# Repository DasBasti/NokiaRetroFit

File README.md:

# Nokia 3210 Retro Fit
Retrofitting a Nokia 3210 with new dual ARM core CPU

* 1GHz dual core CPU
* 1GB DDR3 RAM
* 8GB Memory
* Android N (N7.1.1_1.0.0)

# Status
	[---------100%] BOM generation  
	[--------80%--] Development of schematics / System design  
	[-----50%-----] Pinmuxing of i.MX7  
	[5%-----------] Board layout  
	[0%-----------] Android port  
	[0%-----------] Android applications

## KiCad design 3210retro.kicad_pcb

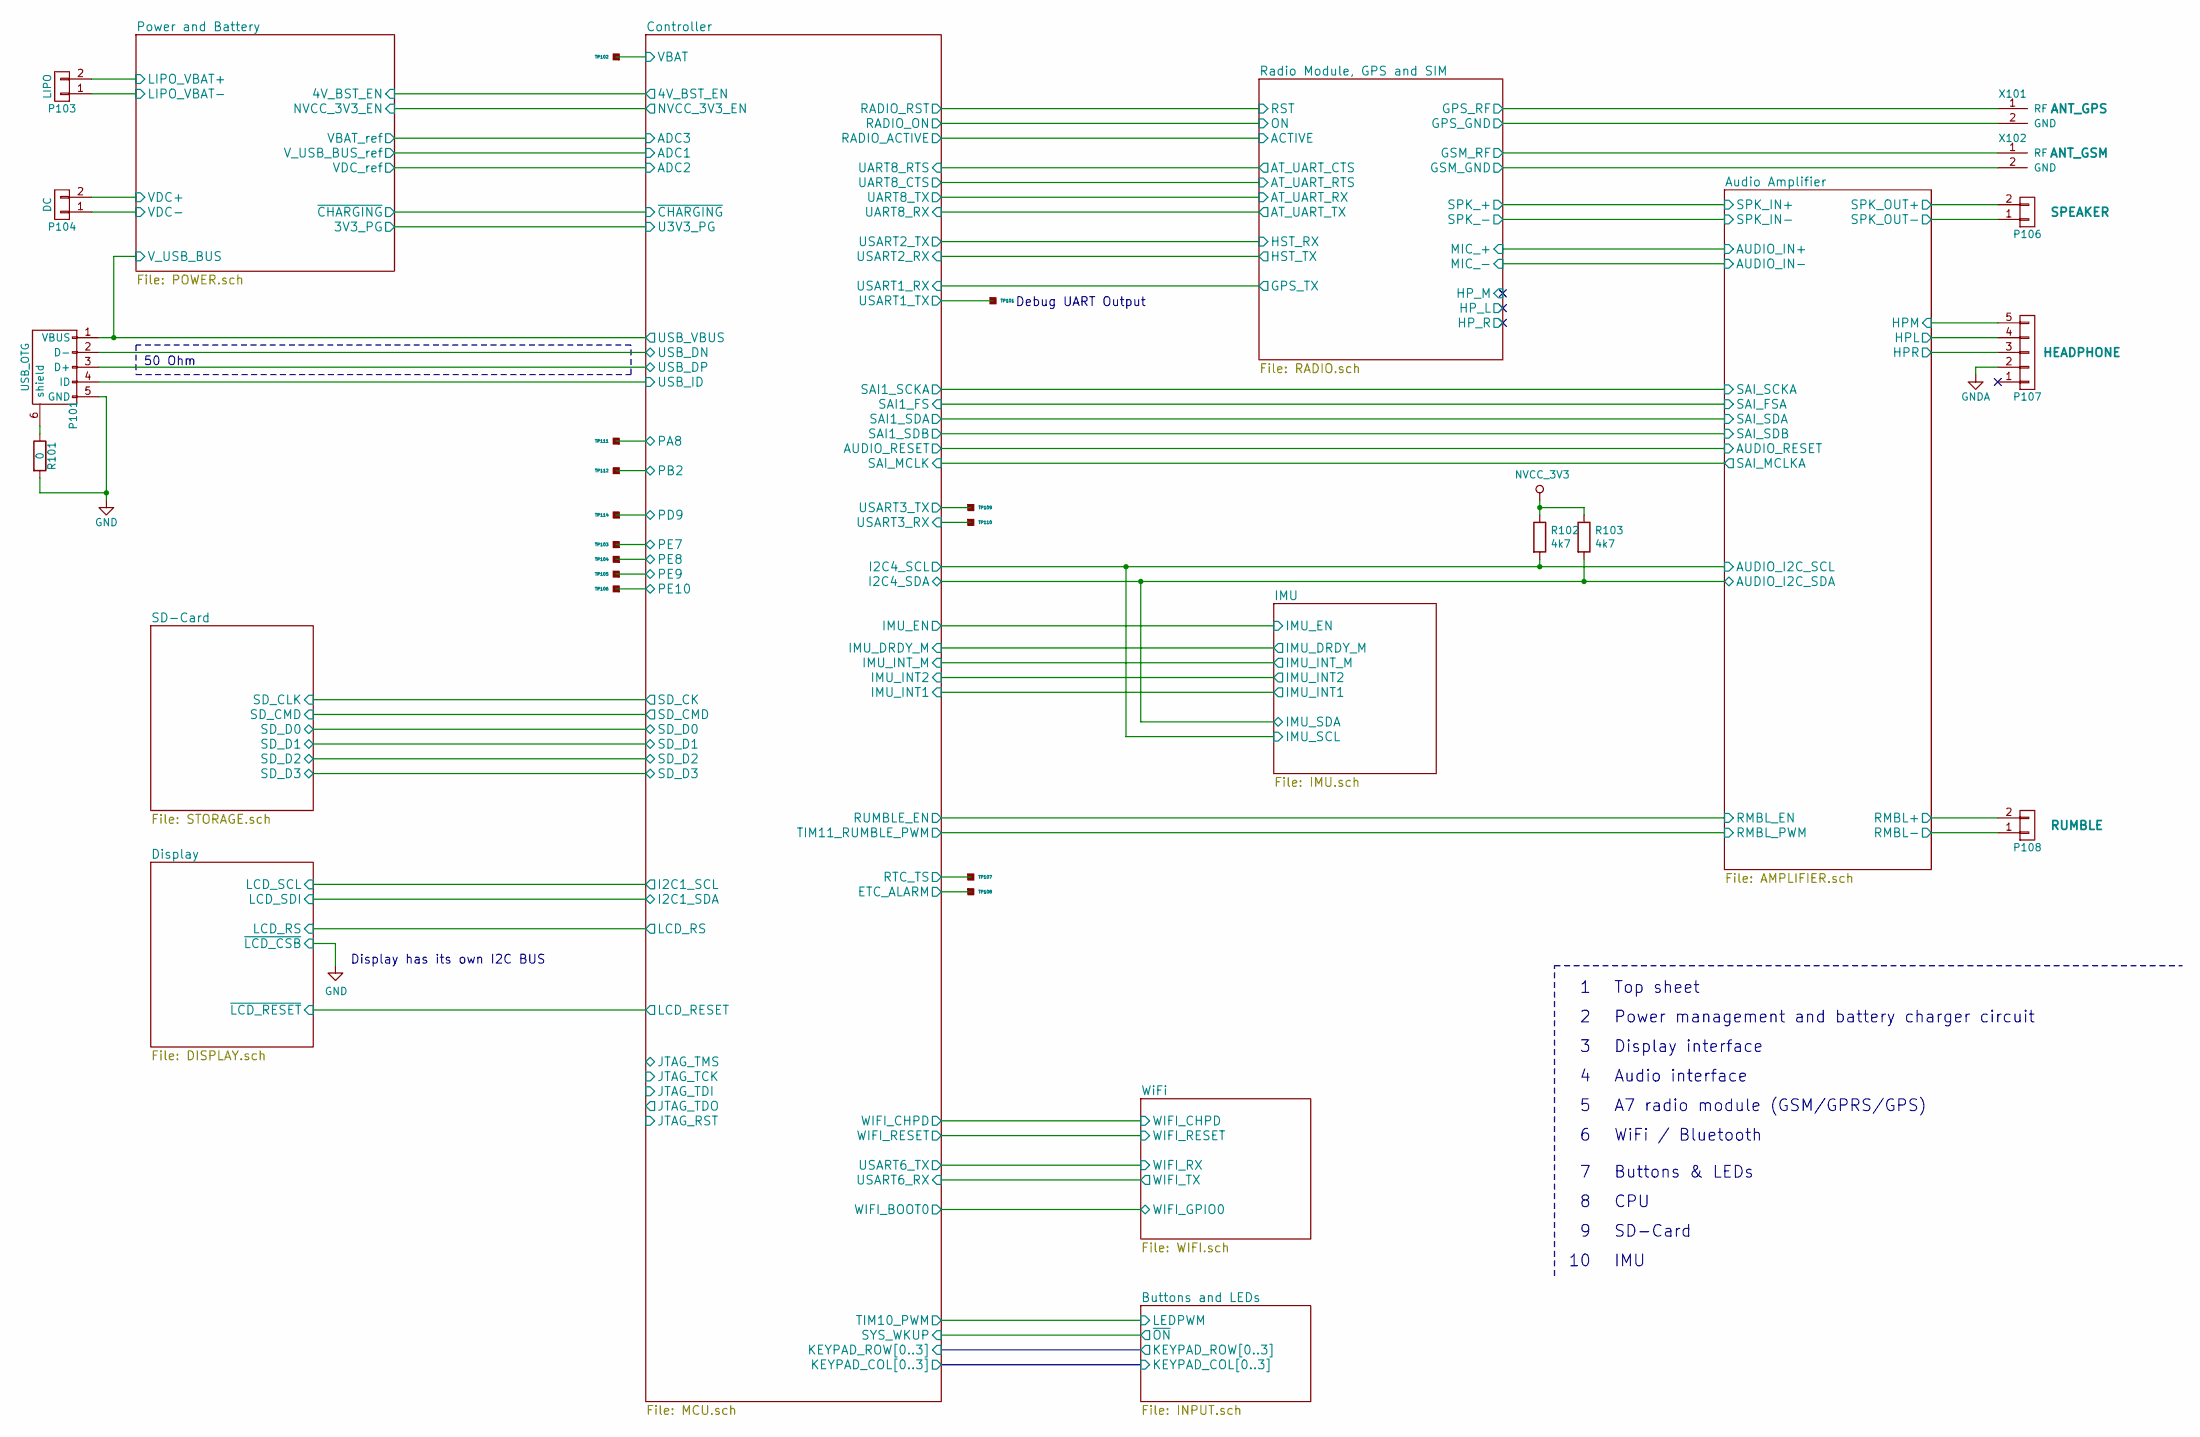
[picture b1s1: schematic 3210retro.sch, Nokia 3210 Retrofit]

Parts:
P101: USB_OTG; USB_Micro-B_10103594-0001LF
P103: LIPO; SolderWirePad_2x_0,8
P104: DC; SolderWirePad_2x_0,8
P106: SPEAKER; SolderWirePad_2x_0,8
P107: HEADPHONE; PJ_320_D
P108: RUMBLE; Rumble_Pads
R101: 0; R_0402_NoSilk
R102, R103: 4k7; R_0402_NoSilk
TP101, TP102, TP103, TP104, TP105, TP106, TP107, TP108, TP109, TP110, TP111, TP112, TP114: TP
X101: ANT_GPS; SolderWirePad_2x_0,8
X102: ANT_GSM; SolderWirePad_2x_0,8

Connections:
+5V: P101.1 (VBUS); also elsewhere on the board
+BATT_LIPO: P103.2; also elsewhere on the board
/Audio Amplifier/AUDIO_I2C_SCL: R102.2; also elsewhere on the board
/Audio Amplifier/AUDIO_I2C_SDA: R103.2; also elsewhere on the board
/Audio Amplifier/HPL: P107.4; also elsewhere on the board
/Audio Amplifier/HPR: P107.3; also elsewhere on the board
/Audio Amplifier/RMBL+: P108.2; also elsewhere on the board
/Audio Amplifier/RMBL-: P108.1; also elsewhere on the board
/Audio Amplifier/SPK_OUT+: P106.2; also elsewhere on the board
/Audio Amplifier/SPK_OUT-: P106.1; also elsewhere on the board
/Controller/ETC_ALARM: TP108.1; also elsewhere on the board
/Controller/PA8: TP111.1; also elsewhere on the board
/Controller/PB2: TP112.1; also elsewhere on the board
/Controller/PD9: TP114.1; also elsewhere on the board
/Controller/PE7: TP103.1; also elsewhere on the board
/Controller/PE8: TP104.1; also elsewhere on the board
/Controller/PE9: TP105.1; also elsewhere on the board
/Controller/PE10: TP106.1; also elsewhere on the board
/Controller/RTC_TS: TP107.1; also elsewhere on the board
/Controller/USART1_TX: TP101.1; also elsewhere on the board
/Controller/USART3_RX: TP110.1; also elsewhere on the board
/Controller/USART3_TX: TP109.1; also elsewhere on the board
/Controller/USB_DN: P101.2 (D-); also elsewhere on the board
/Controller/USB_DP: P101.3 (D+); also elsewhere on the board
/Controller/USB_ID: P101.4 (ID); also elsewhere on the board
/Controller/VBAT: TP102.1; also elsewhere on the board
/Power and Battery/VDC+: P104.2; also elsewhere on the board
/Radio Module, GPS and SIM/GPS_GND: X101.2 (GND); also elsewhere on the board
/Radio Module, GPS and SIM/GPS_RF: X101.1 (RF); also elsewhere on the board
/Radio Module, GPS and SIM/GSM_GND: X102.2 (GND); also elsewhere on the board
/Radio Module, GPS and SIM/GSM_RF: X102.1 (RF); also elsewhere on the board
GND: P101.5 (GND), P103.1, R101.2; also elsewhere on the board
GNDA: P107.2; also elsewhere on the board
GNDREF: P104.1; also elsewhere on the board
NVCC_3V3: R102.1, R103.1; also elsewhere on the board
unnamed: P101.6 (shield), R101.1

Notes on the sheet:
50 Ohm
Top sheet
Power management and battery charger circuit
Display interface
Audio interface
A7 radio module (GSM/GPRS/GPS)
WiFi / Bluetooth
Buttons & LEDs
CPU
Display has its own I2C BUS
Debug UART Output
SD-Card
IMU

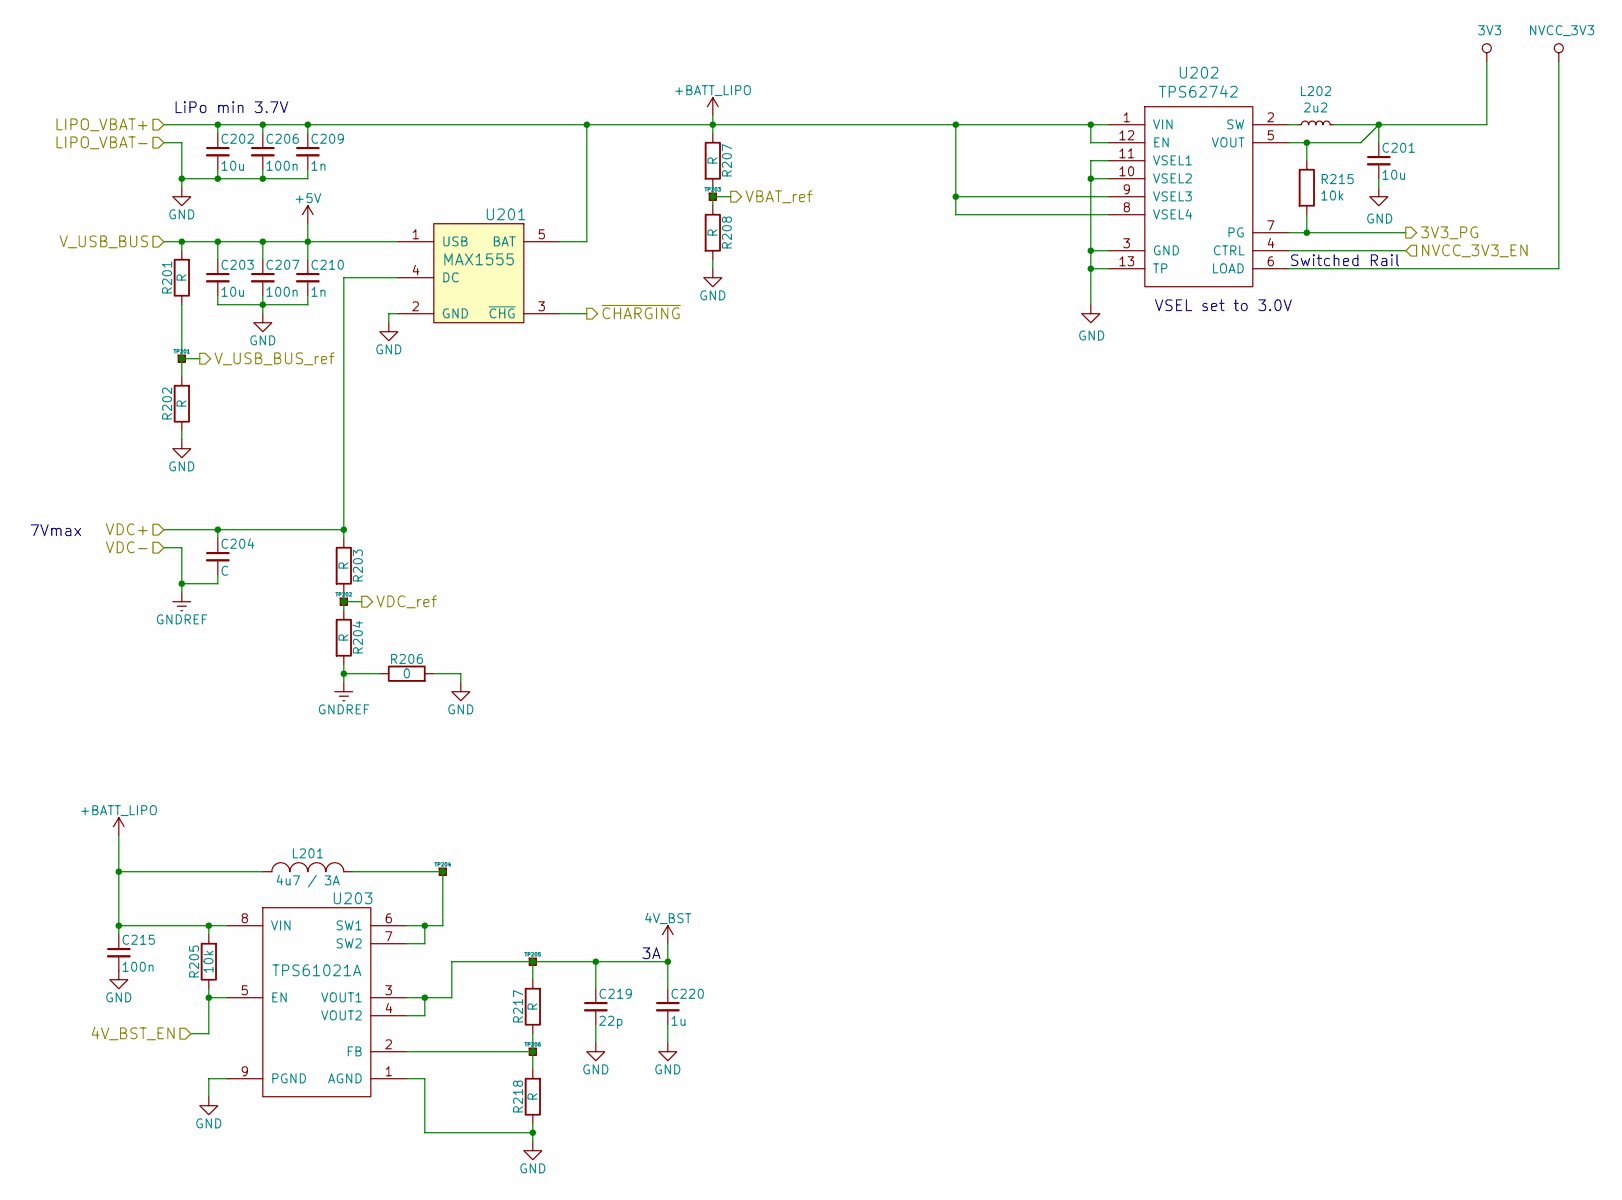
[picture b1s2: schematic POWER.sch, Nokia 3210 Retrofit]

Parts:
C201, C202, C203: 10u; C_0603
C204: C; C_0402_NoSilk
C206, C207, C215: 100n; C_0402_NoSilk
C209, C210: 1n; C_0402_NoSilk
C219: 22p; C_0402_NoSilk
C220: 1u; C_0402_NoSilk
L201: 4u7 / 3A; Choke_SMD_1206_Standard
L202: 2u2; Choke_SMD_1206_Standard
R201, R202, R203, R204, R207, R208, R217, R218: R; R_0402_NoSilk
R205, R215: 10k; R_0402_NoSilk
R206: 0; R_0603
TP201, TP202, TP203, TP204, TP205, TP206: TP
U201: MAX1555; SOT-23-5
U202: TPS62742; TPS6274x
U203: TPS61021A; Texas_S-PVSON-N8_NoThermalVias

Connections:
3V3: C201.1, L202.2, R215.1, U202.5 (VOUT); also elsewhere on the board
4V_BST: C219.1, C220.1, R217.2, TP205.1, U203.3 (VOUT1), U203.4 (VOUT2); also elsewhere on the board
+5V: C203.1, C207.1, C210.1, R201.2, U201.1 (USB); also elsewhere on the board
+BATT_LIPO: C202.1, C206.1, C209.1, C215.1, L201.1, R205.2, R207.1, U201.5 (BAT), U202.1 (VIN), U202.8 (VSEL4), U202.9 (VSEL3), U202.12 (EN), U203.8 (VIN); also elsewhere on the board
/Controller/4V_BST_EN: R205.1, U203.5 (EN); also elsewhere on the board
/Controller/ADC1: R201.1, R202.2, TP201.1; also elsewhere on the board
/Controller/ADC2: R203.2, R204.1, TP202.1; also elsewhere on the board
/Controller/ADC3: R207.2, R208.1, TP203.1; also elsewhere on the board
/Controller/NVCC_3V3_EN: U202.4 (CTRL); also elsewhere on the board
/Controller/~CHARGING: U201.3 (~CHG); also elsewhere on the board
/Power and Battery/3V3_PG: R215.2, U202.7 (PG); also elsewhere on the board
/Power and Battery/VDC+: C204.1, R203.1, U201.4 (DC); also elsewhere on the board
GND: C201.2, C202.2, C203.2, C206.2, C207.2, C209.2, C210.2, C215.2, C219.2, C220.2, R202.1, R206.2, R208.2, R218.1, U201.2 (GND), U202.3 (GND), U202.10 (VSEL2), U202.11 (VSEL1), U202.13 (TP), U203.1 (AGND), U203.9 (PGND); also elsewhere on the board
GNDREF: C204.2, R204.2, R206.1; also elsewhere on the board
NVCC_3V3: U202.6 (LOAD); also elsewhere on the board
unnamed: L201.2, TP204.1, U203.6 (SW1), U203.7 (SW2)
unnamed: L202.1, U202.2 (SW)
unnamed: R217.1, R218.2, TP206.1, U203.2 (FB)

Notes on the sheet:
LiPo min 3.7V
7Vmax
Switched Rail
VSEL set to 3.0V

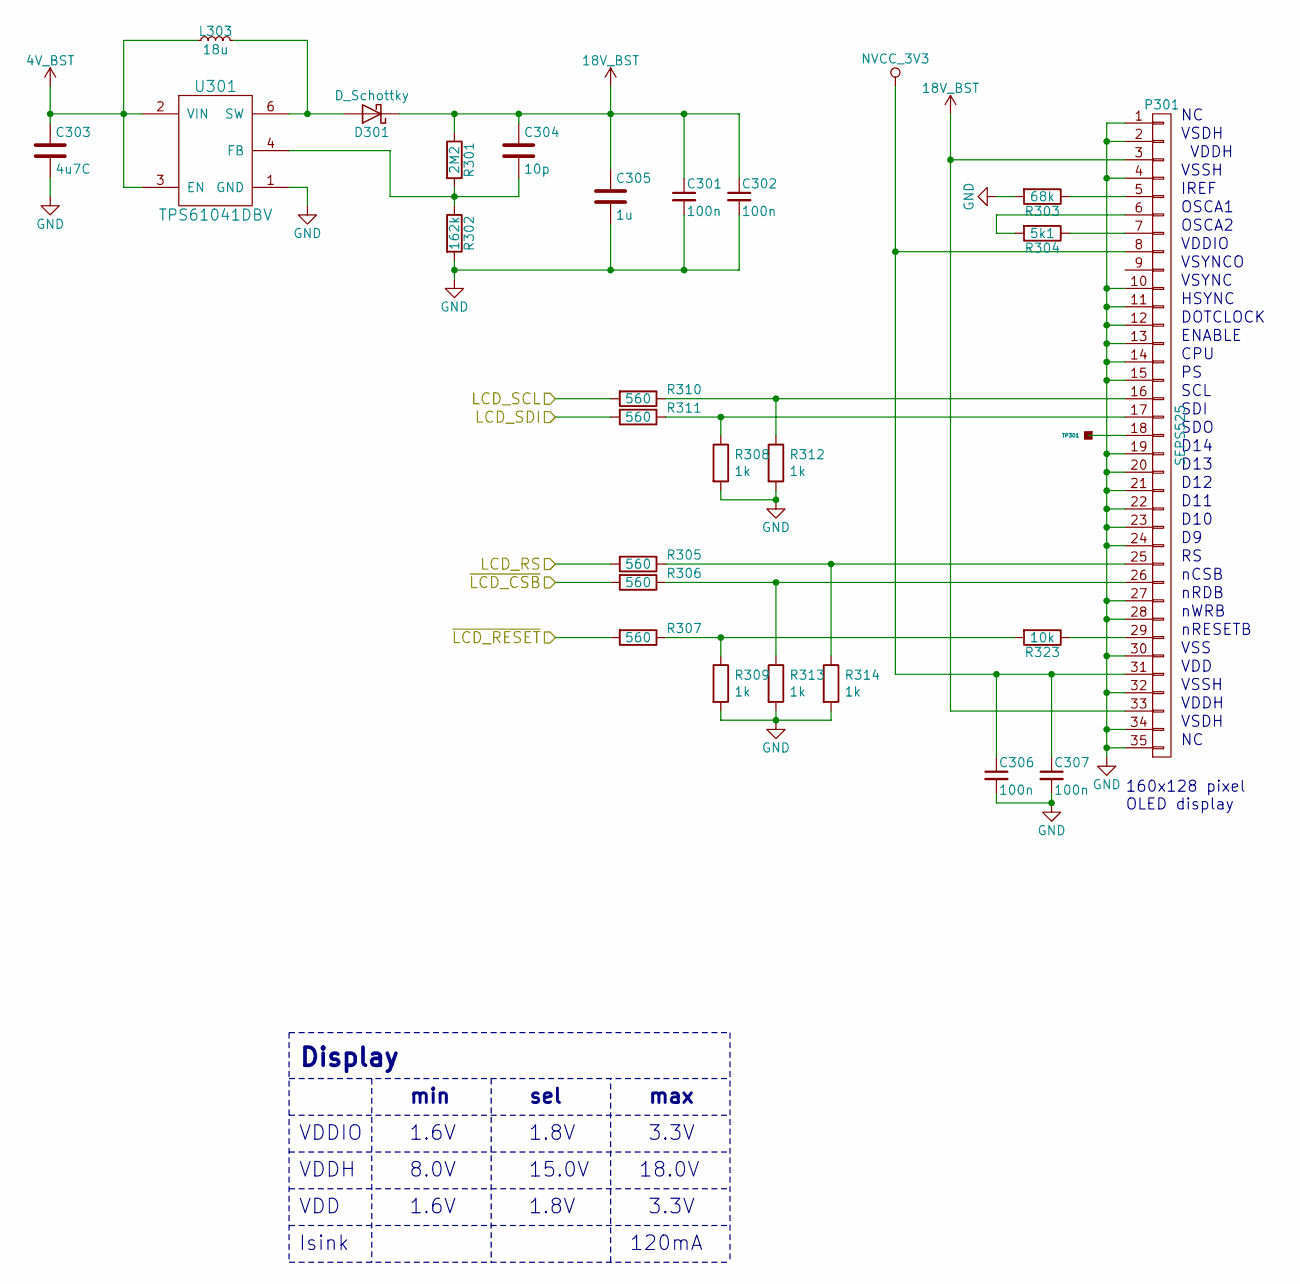
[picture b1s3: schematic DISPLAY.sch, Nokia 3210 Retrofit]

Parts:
C301, C302, C306, C307: 100n; C_0402_NoSilk
C303: 4u7C; C_0402_NoSilk
C304: 10p; C_0402_NoSilk
C305: 1u; C_0402_NoSilk
D301: D_Schottky; D_0805
L303: 18u; Choke_SMD_1206_Standard
P301: SEPS525; FFC-05-35
R301: 2M2; R_0402_NoSilk
R302: 162k; R_0402_NoSilk
R303: 68k; R_0402_NoSilk
R304: 5k1; R_0402_NoSilk
R305, R306, R307, R310, R311: 560; R_0402_NoSilk
R308, R309, R312, R313, R314: 1k; R_0402_NoSilk
R323: 10k; R_0402_NoSilk
TP301: TP
U301: TPS61041DBV; DFN-6-1EP_2x2mm_Pitch0.65mm

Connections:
4V_BST: C303.1, L303.2, U301.2 (VIN), U301.3 (EN); also elsewhere on the board
18V_BST: C301.1, C302.1, C304.1, C305.1, D301.1 (K), P301.3, P301.33, R301.1
/Controller/I2C1_SCL: R310.2; also elsewhere on the board
/Controller/I2C1_SDA: R311.2; also elsewhere on the board
/Controller/LCD_RESET: R307.2; also elsewhere on the board
/Controller/LCD_RS: R305.2; also elsewhere on the board
GND: C301.2, C302.2, C303.2, C305.2, C306.2, C307.2, P301.1, P301.2, P301.4, P301.10, P301.11, P301.12, P301.13, P301.14, P301.15, P301.19, P301.20, P301.21, P301.22, P301.23, P301.24, P301.27, P301.28, P301.30, P301.32, P301.34, P301.35, R302.2, R303.2, R306.2, R308.2, R309.2, R312.2, R313.2, R314.2, U301.1 (GND); also elsewhere on the board
NVCC_3V3: C306.1, C307.1, P301.8, P301.31; also elsewhere on the board
unnamed: C304.2, R301.2, R302.1, U301.4 (FB)
unnamed: D301.2 (A), L303.1, U301.6 (SW)
unnamed: P301.5, R303.1
unnamed: P301.6, R304.2
unnamed: P301.7, R304.1
unnamed: P301.16, R310.1, R312.1
unnamed: P301.17, R308.1, R311.1
unnamed: P301.18, TP301.1
unnamed: P301.25, R305.1, R314.1
unnamed: P301.26, R306.1, R313.1
unnamed: P301.29, R323.1
unnamed: R307.1, R309.1, R323.2

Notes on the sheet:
VDDIO
VDDH
VDD
Display
1.6V
3.3V
8.0V
18.0V
min
max
160x128 pixel OLED display
Isink
120mA
sel
1.8V
15.0V
VSDH
VSSH
IREF
OSCA1
OSCA2
VSYNCO
VSYNC
HSYNC
DOTCLOCK
ENABLE
CPU
SCL
SDI
SDO
D14
D13
D12
D11
D10
nCSB
nWRB
nRESETB
VSS
nRDB

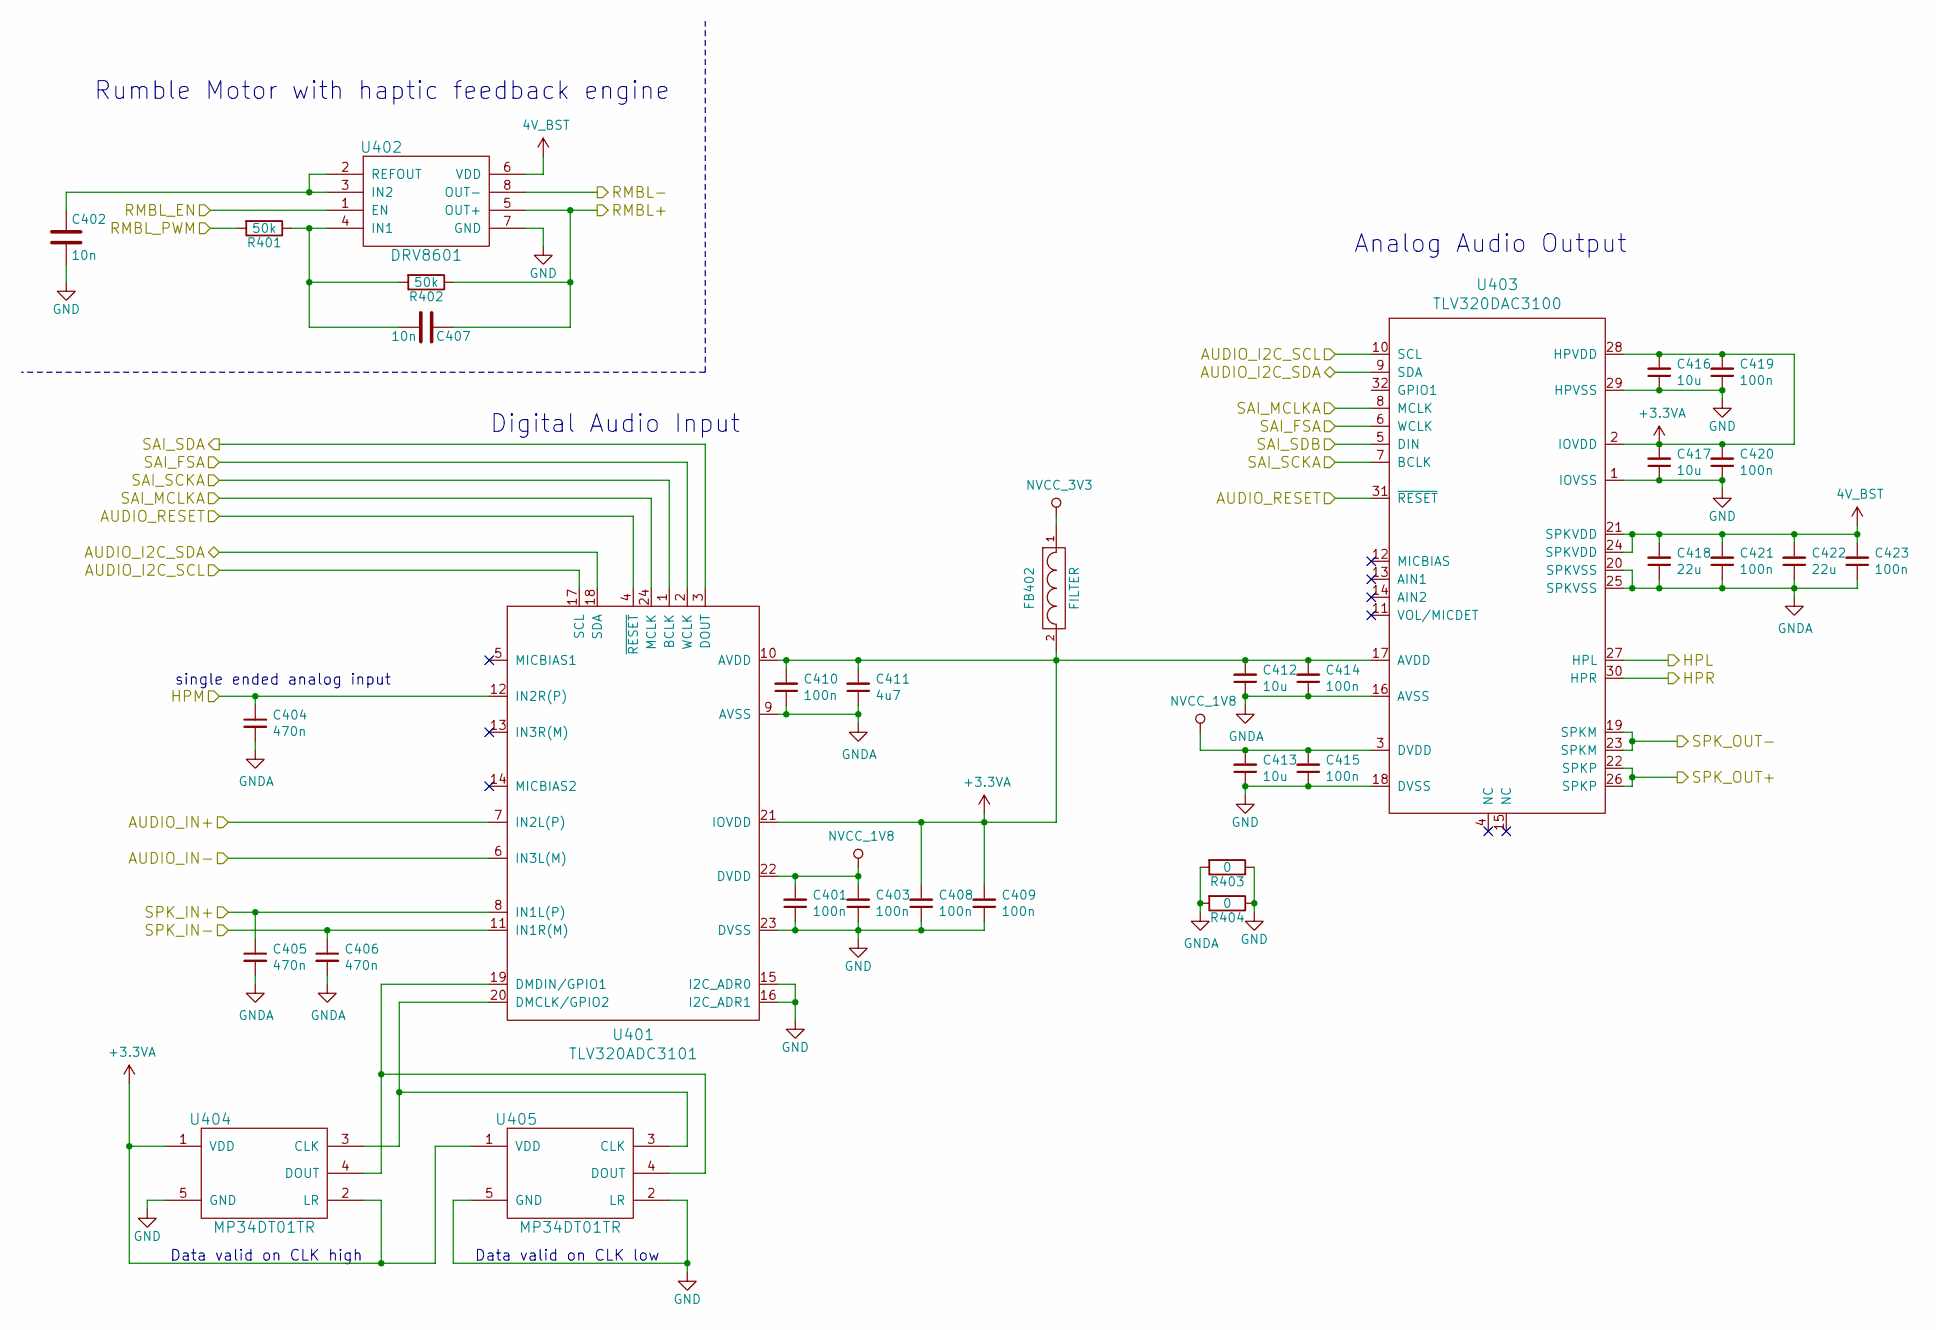
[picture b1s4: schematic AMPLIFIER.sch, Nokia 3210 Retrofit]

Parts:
C401, C403, C408, C409, C410, C414, C415, C419, C420, C421, C423: 100n; C_0402_NoSilk
C402, C407: 10n; C_0402_NoSilk
C404, C405, C406: 470n; C_0402_NoSilk
C411: 4u7; C_0402_NoSilk
C412, C413, C416, C417: 10u; C_0402_NoSilk
C418, C422: 22u; C_0402_NoSilk
FB402: FILTER; Choke_SMD_1206_Standard
R401, R402: 50k; R_0402_NoSilk
R403, R404: 0; R_0402_NoSilk
U401: TLV320ADC3101; QFN-24-1EP_4x4mm_Pitch0.5mm
U402: DRV8601; DFN-8-1EP_3x3mm_Pitch0.65mm
U403: TLV320DAC3100; QFN-32-1EP_5x5mm_Pitch0.5mm
U404, U405: MP34DT01TR; MP34DT01_NoGroundRing

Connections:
4V_BST: C418.2, C421.2, C422.2, C423.2, U402.6 (VDD), U403.21 (SPKVDD), U403.24 (SPKVDD); also elsewhere on the board
+3.3VA: C408.2, C409.2, C410.2, C411.2, C412.2, C414.2, C416.2, C417.2, C419.2, C420.2, FB402.2, U401.10 (AVDD), U401.21 (IOVDD), U403.2 (IOVDD), U403.17 (AVDD), U403.28 (HPVDD), U404.1 (VDD), U404.2 (LR), U405.1 (VDD)
/Audio Amplifier/AUDIO_I2C_SCL: U401.17 (SCL), U403.10 (SCL); also elsewhere on the board
/Audio Amplifier/AUDIO_I2C_SDA: U401.18 (SDA), U403.9 (SDA); also elsewhere on the board
/Audio Amplifier/AUDIO_IN+: U401.7 (IN2L(P)); also elsewhere on the board
/Audio Amplifier/AUDIO_IN-: U401.6 (IN3L(M)); also elsewhere on the board
/Audio Amplifier/AUDIO_RESET: U401.4 (~RESET), U403.31 (~RESET); also elsewhere on the board
/Audio Amplifier/HPL: U403.27 (HPL); also elsewhere on the board
/Audio Amplifier/HPM: C404.1, U401.12 (IN2R(P))
/Audio Amplifier/HPR: U403.30 (HPR); also elsewhere on the board
/Audio Amplifier/RMBL+: C407.1, R402.1, U402.5 (OUT+); also elsewhere on the board
/Audio Amplifier/RMBL-: U402.8 (OUT-); also elsewhere on the board
/Audio Amplifier/RMBL_EN: U402.1 (EN); also elsewhere on the board
/Audio Amplifier/RMBL_PWM: R401.2; also elsewhere on the board
/Audio Amplifier/SPK_OUT+: U403.22 (SPKP), U403.26 (SPKP); also elsewhere on the board
/Audio Amplifier/SPK_OUT-: U403.19 (SPKM), U403.23 (SPKM); also elsewhere on the board
/Controller/SAI1_FS: U401.2 (WCLK), U403.6 (WCLK); also elsewhere on the board
/Controller/SAI1_SCKA: U401.1 (BCLK), U403.7 (BCLK); also elsewhere on the board
/Controller/SAI1_SDA: U401.3 (DOUT); also elsewhere on the board
/Controller/SAI1_SDB: U403.5 (DIN); also elsewhere on the board
/Controller/SAI_MCLK: U401.24 (MCLK), U403.8 (MCLK); also elsewhere on the board
/Radio Module, GPS and SIM/SPK_+: C405.1, U401.8 (IN1L(P)); also elsewhere on the board
/Radio Module, GPS and SIM/SPK_-: C406.1, U401.11 (IN1R(M)); also elsewhere on the board
GND: C401.1, C402.2, C403.1, C408.1, C409.1, C413.1, C415.1, C416.1, C417.1, C419.1, C420.1, R403.1, R404.1, U401.15 (I2C_ADR0), U401.16 (I2C_ADR1), U401.23 (DVSS), U402.7 (GND), U402.9 (PAD), U403.1 (IOVSS), U403.18 (DVSS), U403.29 (HPVSS), U404.5 (GND), U405.2 (LR), U405.5 (GND); also elsewhere on the board
GNDA: C404.2, C405.2, C406.2, C410.1, C411.1, C412.1, C414.1, C418.1, C421.1, C422.1, C423.1, R403.2, R404.2, U401.9 (AVSS), U403.16 (AVSS), U403.20 (SPKVSS), U403.25 (SPKVSS); also elsewhere on the board
NVCC_1V8: C401.2, C403.2, C413.2, C415.2, U401.22 (DVDD), U403.3 (DVDD); also elsewhere on the board
NVCC_3V3: FB402.1; also elsewhere on the board
unnamed: C402.1, U402.2 (REFOUT), U402.3 (IN2)
unnamed: C407.2, R401.1, R402.2, U402.4 (IN1)
unnamed: U401.19 (DMDIN/GPIO1), U404.4 (DOUT), U405.4 (DOUT)
unnamed: U401.20 (DMCLK/GPIO2), U404.3 (CLK), U405.3 (CLK)

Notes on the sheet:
Data valid on CLK high
Data valid on CLK low
Rumble Motor with haptic feedback engine
single ended analog input
Digital Audio Input
Analog Audio Output

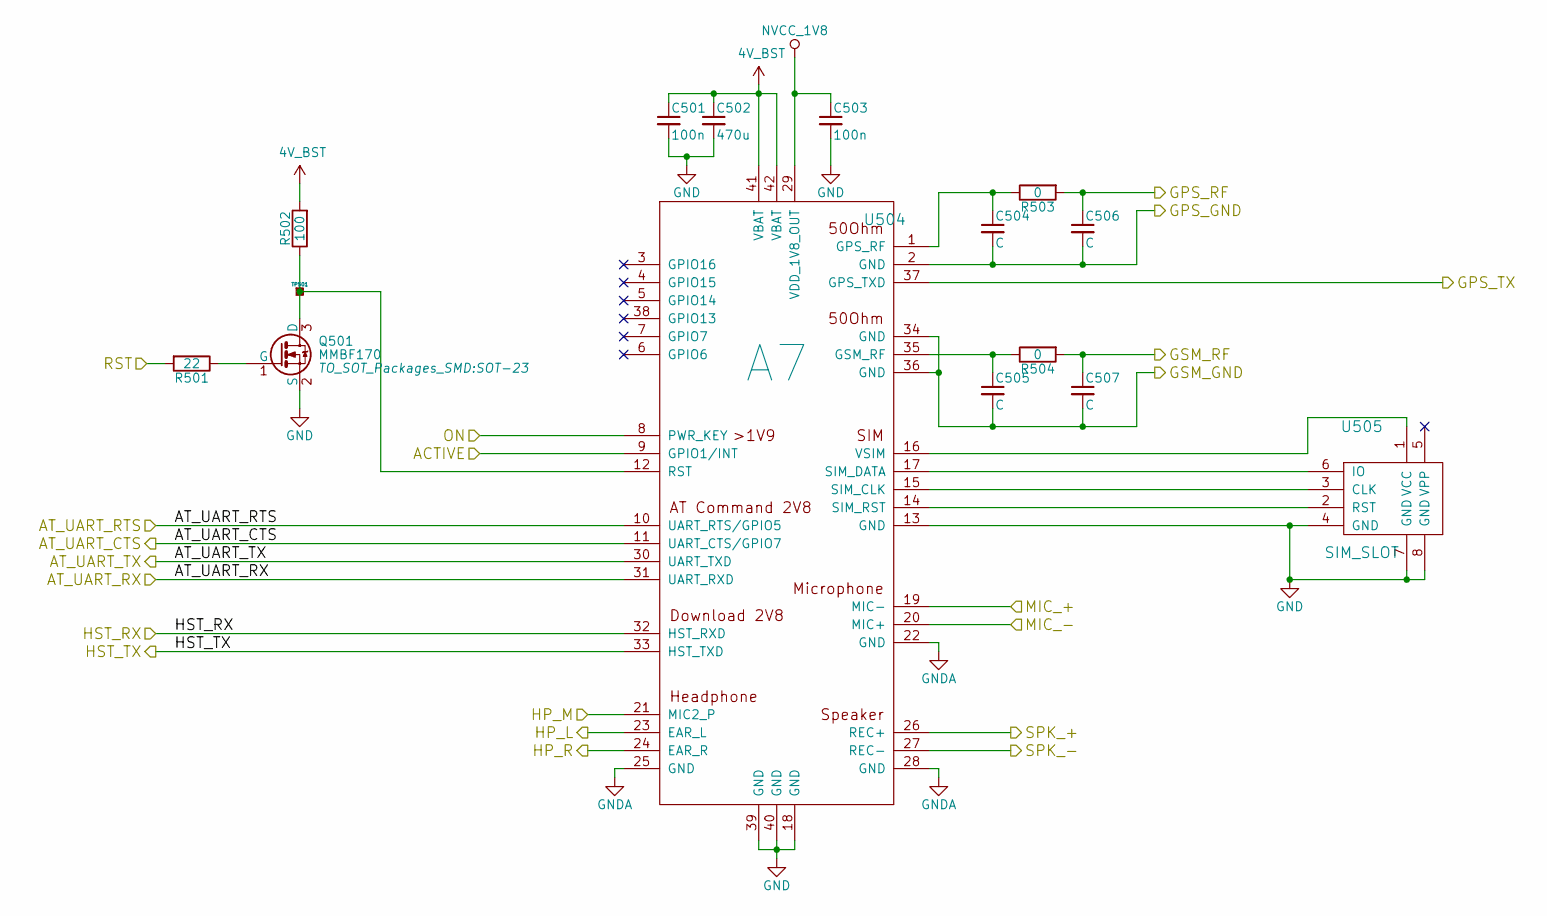
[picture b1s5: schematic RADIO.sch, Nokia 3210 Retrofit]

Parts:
C501, C503: 100n; C_0402_NoSilk
C502: 470u; C_0603
C504, C505, C506, C507: C; C_0402_NoSilk
Q501: MMBF170; SOT-23
R501: 22; R_0402_NoSilk
R502: 100; R_0402_NoSilk
R503, R504: 0; R_0402_NoSilk
TP501: TP
U504: A7
U505: SIM_SLOT; SIM

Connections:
4V_BST: C501.1, C502.1, R502.2, U504.41 (VBAT), U504.42 (VBAT); also elsewhere on the board
/Audio Amplifier/AUDIO_IN+: U504.19 (MIC-); also elsewhere on the board
/Audio Amplifier/AUDIO_IN-: U504.20 (MIC+); also elsewhere on the board
/Controller/RADIO_RST: R501.2; also elsewhere on the board
/Radio Module, GPS and SIM/ACTIVE: U504.9 (GPIO1/INT); also elsewhere on the board
/Radio Module, GPS and SIM/AT_UART_CTS: U504.11 (UART_CTS/GPIO7); also elsewhere on the board
/Radio Module, GPS and SIM/AT_UART_RTS: U504.10 (UART_RTS/GPIO5); also elsewhere on the board
/Radio Module, GPS and SIM/AT_UART_RX: U504.31 (UART_RXD); also elsewhere on the board
/Radio Module, GPS and SIM/AT_UART_TX: U504.30 (UART_TXD); also elsewhere on the board
/Radio Module, GPS and SIM/GPS_GND: C504.2, C506.2, U504.2 (GND); also elsewhere on the board
/Radio Module, GPS and SIM/GPS_RF: C506.1, R503.2; also elsewhere on the board
/Radio Module, GPS and SIM/GPS_TX: U504.37 (GPS_TXD); also elsewhere on the board
/Radio Module, GPS and SIM/GSM_GND: C505.2, C507.2, U504.34 (GND), U504.36 (GND); also elsewhere on the board
/Radio Module, GPS and SIM/GSM_RF: C507.1, R504.2; also elsewhere on the board
/Radio Module, GPS and SIM/HP_L: U504.23 (EAR_L)
/Radio Module, GPS and SIM/HP_M: U504.21 (MIC2_P)
/Radio Module, GPS and SIM/HP_R: U504.24 (EAR_R)
/Radio Module, GPS and SIM/HST_RX: U504.32 (HST_RXD); also elsewhere on the board
/Radio Module, GPS and SIM/HST_TX: U504.33 (HST_TXD); also elsewhere on the board
/Radio Module, GPS and SIM/ON: U504.8 (PWR_KEY); also elsewhere on the board
/Radio Module, GPS and SIM/SPK_+: U504.26 (REC+); also elsewhere on the board
/Radio Module, GPS and SIM/SPK_-: U504.27 (REC-); also elsewhere on the board
GND: C501.2, C502.2, C503.2, Q501.2 (S), U504.13 (GND), U504.18 (GND), U504.39 (GND), U504.40 (GND), U505.4 (GND), U505.7 (GND), U505.8 (GND); also elsewhere on the board
GNDA: U504.22 (GND), U504.25 (GND), U504.28 (GND); also elsewhere on the board
NVCC_1V8: C503.1, U504.29 (VDD_1V8_OUT); also elsewhere on the board
unnamed: C504.1, R503.1, U504.1 (GPS_RF)
unnamed: C505.1, R504.1, U504.35 (GSM_RF)
unnamed: Q501.1 (G), R501.1
unnamed: Q501.3 (D), R502.1, TP501.1, U504.12 (RST)
unnamed: U504.14 (SIM_RST), U505.2 (RST)
unnamed: U504.15 (SIM_CLK), U505.3 (CLK)
unnamed: U504.16 (VSIM), U505.1 (VCC)
unnamed: U504.17 (SIM_DATA), U505.6 (IO)

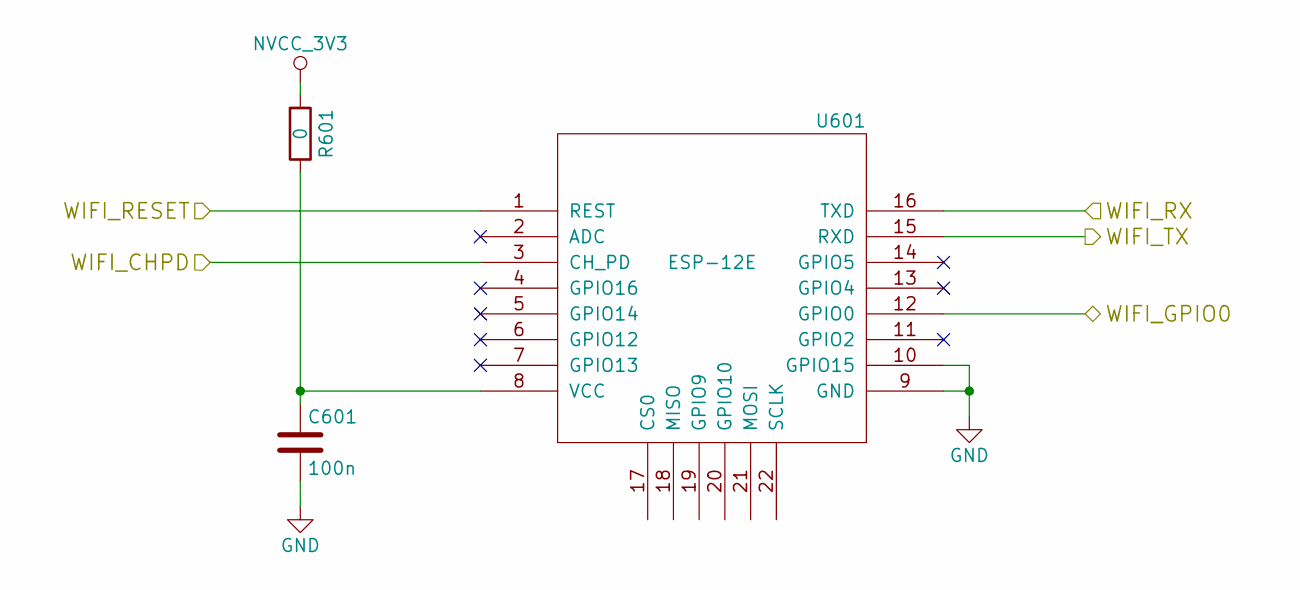
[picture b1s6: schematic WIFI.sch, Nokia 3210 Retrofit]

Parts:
C601: 100n; C_0402_NoSilk
R601: 0; R_0402_NoSilk
U601: ESP-12E

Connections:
/Controller/USART6_RX: U601.15 (RXD); also elsewhere on the board
/Controller/USART6_TX: U601.16 (TXD); also elsewhere on the board
/Controller/WIFI_BOOT0: U601.12 (GPIO0); also elsewhere on the board
/Controller/WIFI_CHPD: U601.3 (CH_PD); also elsewhere on the board
/Controller/WIFI_RESET: U601.1 (REST); also elsewhere on the board
GND: C601.2, U601.9 (GND), U601.10 (GPIO15); also elsewhere on the board
NVCC_3V3: R601.2; also elsewhere on the board
unnamed: C601.1, R601.1, U601.8 (VCC)

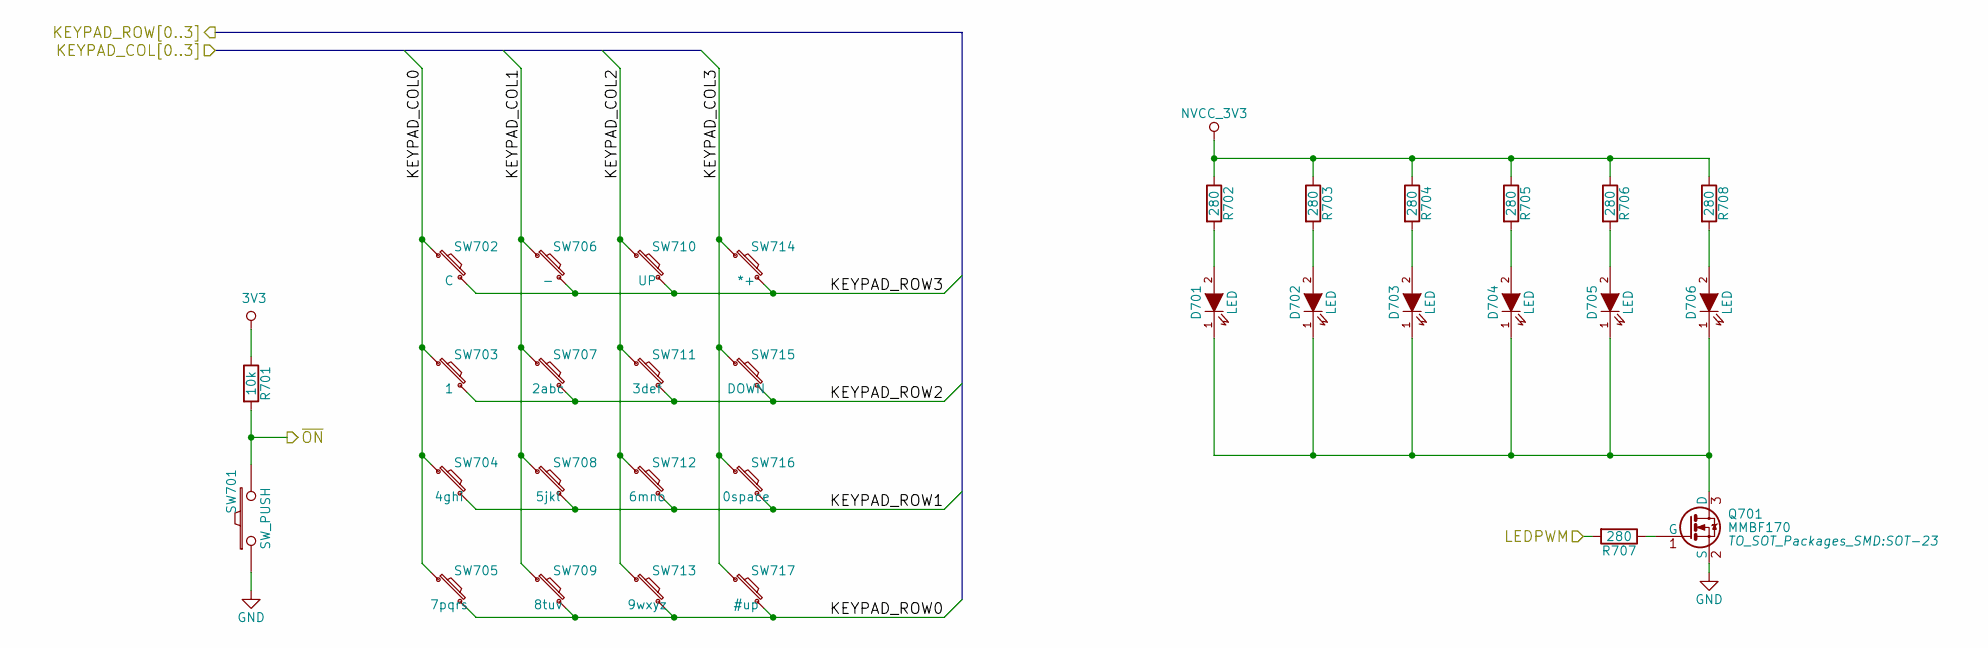
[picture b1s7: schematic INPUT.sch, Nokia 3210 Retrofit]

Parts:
D701, D702, D703, D704, D705, D706: LED; LED_0603
Q701: MMBF170; SOT-23
R701: 10k; R_0402_NoSilk
R702, R703, R704, R705, R706, R707, R708: 280; R_0402_NoSilk
SW701: SW_PUSH; TS-015A
SW702: C; Foil_Button
SW703: 1; Foil_Button
SW704: 4ghi; Foil_Button
SW705: 7pqrs; Foil_Button
SW706: -; Foil_Button
SW707: 2abc; Foil_Button
SW708: 5jkl; Foil_Button
SW709: 8tuv; Foil_Button
SW710: UP; Foil_Button
SW711: 3def; Foil_Button
SW712: 6mno; Foil_Button
SW713: 9wxyz; Foil_Button
SW714: *+; Foil_Button
SW715: DOWN; Foil_Button
SW716: 0space; Foil_Button
SW717: #up; Foil_Button

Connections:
3V3: R701.1; also elsewhere on the board
/Buttons and LEDs/KEYPAD_COL0: SW702.1, SW703.1, SW704.1, SW705.1; also elsewhere on the board
/Buttons and LEDs/KEYPAD_COL1: SW706.1, SW707.1, SW708.1, SW709.1; also elsewhere on the board
/Buttons and LEDs/KEYPAD_COL2: SW710.1, SW711.1, SW712.1, SW713.1; also elsewhere on the board
/Buttons and LEDs/KEYPAD_COL3: SW714.1, SW715.1, SW716.1, SW717.1; also elsewhere on the board
/Buttons and LEDs/KEYPAD_ROW0: SW705.2, SW709.2, SW713.2, SW717.2; also elsewhere on the board
/Buttons and LEDs/KEYPAD_ROW1: SW704.2, SW708.2, SW712.2, SW716.2; also elsewhere on the board
/Buttons and LEDs/KEYPAD_ROW2: SW703.2, SW707.2, SW711.2, SW715.2; also elsewhere on the board
/Buttons and LEDs/KEYPAD_ROW3: SW702.2, SW706.2, SW710.2, SW714.2; also elsewhere on the board
/Buttons and LEDs/LEDPWM: R707.2; also elsewhere on the board
/Controller/SYS_WKUP: R701.2, SW701.2; also elsewhere on the board
GND: Q701.2 (S), SW701.1; also elsewhere on the board
NVCC_3V3: R702.1, R703.1, R704.1, R705.1, R706.1, R708.1; also elsewhere on the board
unnamed: D701.1 (K), D702.1 (K), D703.1 (K), D704.1 (K), D705.1 (K), D706.1 (K), Q701.3 (D)
unnamed: D701.2 (A), R702.2
unnamed: D702.2 (A), R703.2
unnamed: D703.2 (A), R704.2
unnamed: D704.2 (A), R705.2
unnamed: D705.2 (A), R706.2
unnamed: D706.2 (A), R708.2
unnamed: Q701.1 (G), R707.1
